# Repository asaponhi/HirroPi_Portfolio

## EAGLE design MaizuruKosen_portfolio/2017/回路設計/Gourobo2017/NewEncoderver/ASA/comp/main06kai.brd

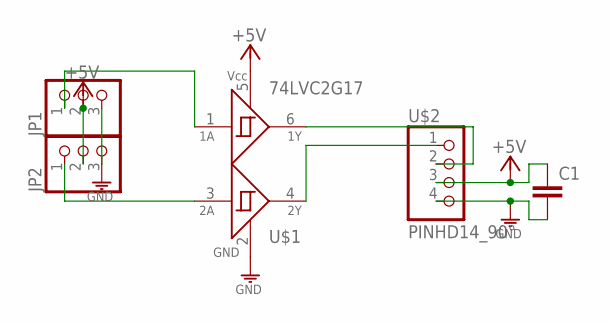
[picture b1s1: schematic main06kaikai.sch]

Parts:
C1: MLCC-2; MLCC_25
JP1, JP2: PINHD-13_90°; 1*3_90
U$1: 74LVC2G17
U$2: PINHD14_90°; 1*4_90

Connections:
+5V: C1.1, JP1.2, JP2.2, U$1.5, U$2.3
GND: C1.2, JP1.3, JP2.3, U$1.2, U$2.4
unnamed: U$1.6, U$2.2
unnamed: U$1.4, U$2.1
unnamed: JP1.1, U$1.1
unnamed: JP2.1, U$1.3

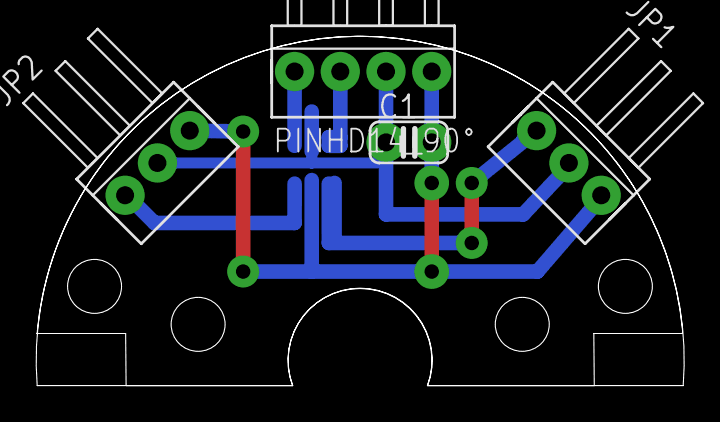
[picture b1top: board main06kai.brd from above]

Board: 2 copper layers, 36.0 x 19.4 mm, 5 parts (1 on the bottom side), 6 nets.

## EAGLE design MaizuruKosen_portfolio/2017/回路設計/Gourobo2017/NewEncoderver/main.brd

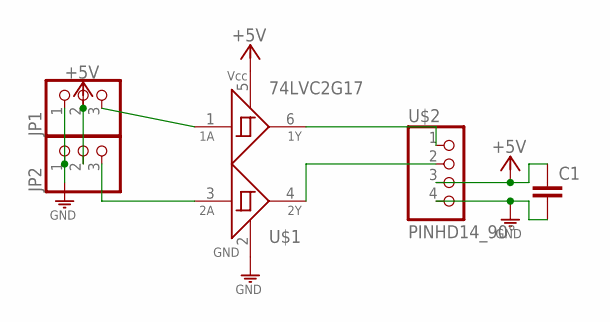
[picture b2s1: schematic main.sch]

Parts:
C1: MLCC-2; MLCC_25
JP1, JP2: PINHD-13_90°; 1*3_90
U$1: 74LVC2G17
U$2: PINHD14_90°; 1*4_90

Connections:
+5V: C1.1, JP1.2, JP2.2, U$1.5, U$2.3
GND: C1.2, JP1.1, JP2.1, U$1.2, U$2.4
unnamed: U$1.6, U$2.1
unnamed: U$1.4, U$2.2
unnamed: JP1.3, U$1.1
unnamed: JP2.3, U$1.3

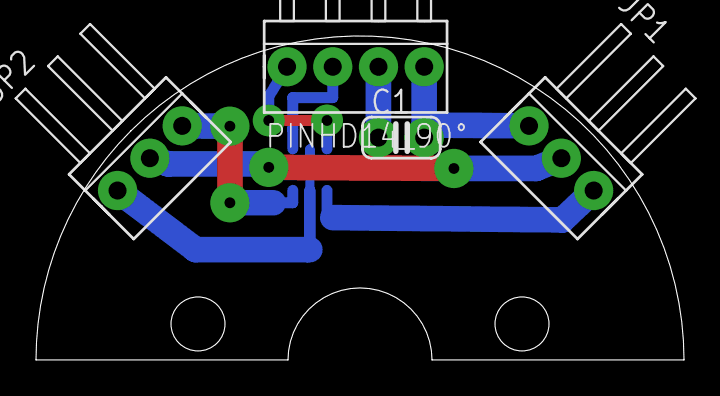
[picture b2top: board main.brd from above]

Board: 2 copper layers, 36.0 x 18.0 mm, 5 parts (1 on the bottom side), 6 nets.

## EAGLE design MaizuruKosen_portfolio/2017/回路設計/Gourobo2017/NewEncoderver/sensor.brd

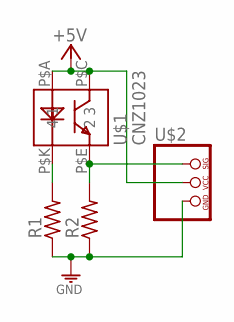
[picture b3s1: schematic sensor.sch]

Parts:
R1, R2: RESISTORS; R_3216
U$1: CNZ1023
U$2: PINHD-SENSOR; 1*03(KIKAKU)

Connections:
+5V: U$1.P$A (1), U$1.P$C (3), U$2.VCC
GND: R1.1, R2.1, U$2.GND
unnamed: R1.2, U$1.P$K (4)
unnamed: R2.2, U$1.P$E (2), U$2.SIG

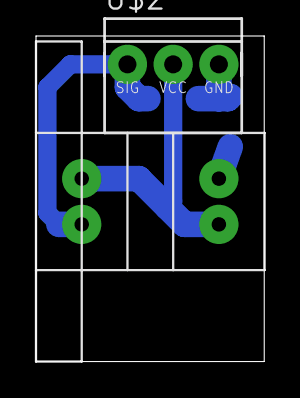
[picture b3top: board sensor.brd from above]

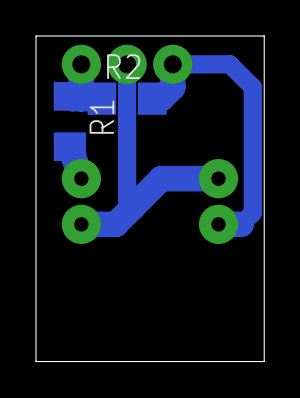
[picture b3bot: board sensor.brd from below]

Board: 2 copper layers, 12.7 x 18.1 mm, 4 parts (2 on the bottom side), 4 nets.

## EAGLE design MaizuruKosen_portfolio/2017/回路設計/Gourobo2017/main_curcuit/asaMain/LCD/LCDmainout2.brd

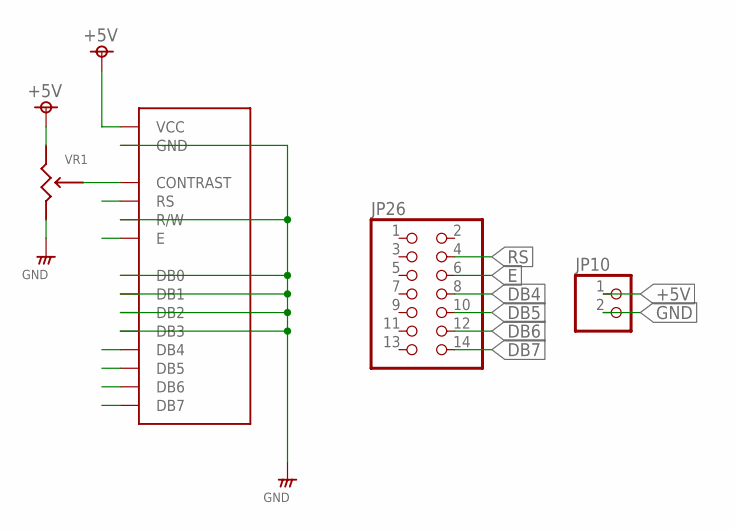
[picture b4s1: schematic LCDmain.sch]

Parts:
JP10: PINHD-1X2"; 1*02
JP26: PINHD-2X7; 2X07
U$1: LCD_16X2
VR1: R-TRIM-3-L; R_TRIM3

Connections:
+5V: JP10.1, U$1.P$1 (VCC), VR1.1
DB4: JP26.8, U$1.P$11 (DB4)
DB5: JP26.10, U$1.P$12 (DB5)
DB6: JP26.12, U$1.P$13 (DB6)
DB7: JP26.14, U$1.P$14 (DB7)
E: JP26.6, U$1.P$6 (E)
GND: JP10.2, U$1.P$2 (GND), U$1.P$5 (R/W), U$1.P$7 (DB0), U$1.P$8 (DB1), U$1.P$9 (DB2), U$1.P$10 (DB3), VR1.3
unnamed: U$1.P$3 (CONTRAST), VR1.2
RS: JP26.4, U$1.P$4 (RS)

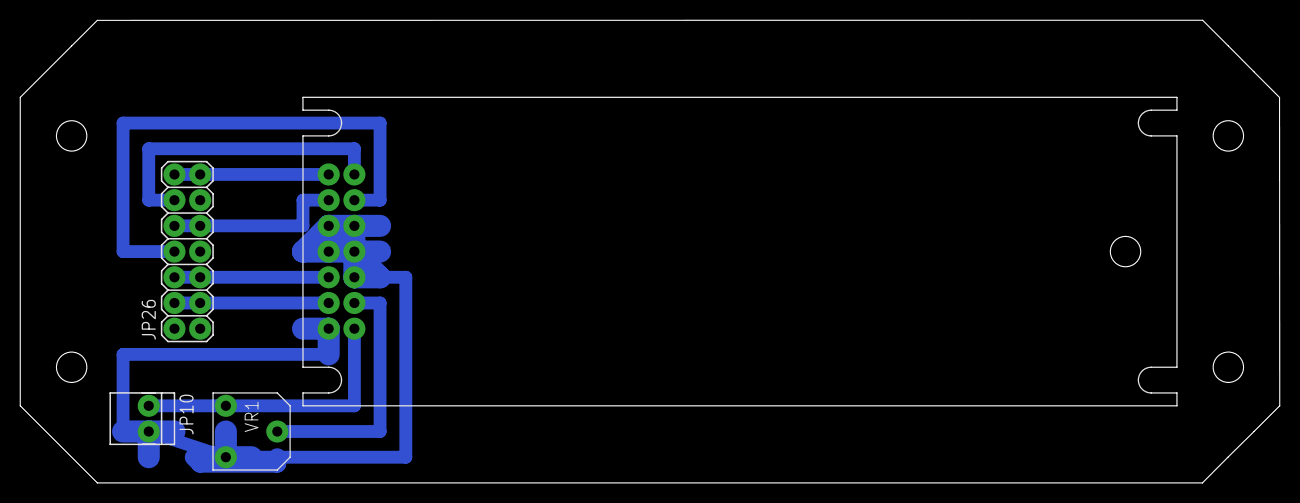
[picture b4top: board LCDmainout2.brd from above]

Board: 2 copper layers, 124.5 x 45.7 mm, 4 parts (0 on the bottom side), 9 nets.

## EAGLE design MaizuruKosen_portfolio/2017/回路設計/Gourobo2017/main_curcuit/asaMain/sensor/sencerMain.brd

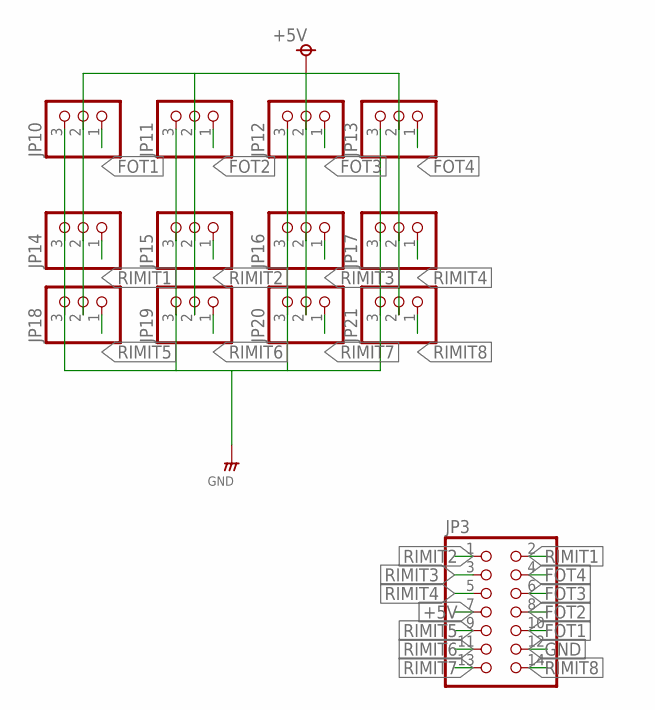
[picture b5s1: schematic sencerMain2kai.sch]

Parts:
JP3: PINHD-2X7; 2X07
JP10, JP11, JP12, JP13, JP14, JP15, JP16, JP17, JP18, JP19, JP20, JP21: PINHD-1X3-1; 1*03

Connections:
+5V: JP3.7, JP10.2, JP11.2, JP12.2, JP13.2, JP14.2, JP15.2, JP16.2, JP17.2, JP18.2, JP19.2, JP20.2, JP21.2
FOT1: JP3.10, JP10.1 (3)
FOT2: JP3.8, JP11.1 (3)
FOT3: JP3.6, JP12.1 (3)
FOT4: JP3.4, JP13.1 (3)
GND: JP3.12, JP10.3 (1), JP11.3 (1), JP13.3 (1), JP14.3 (1), JP15.3 (1), JP17.3 (1), JP18.3 (1), JP19.3 (1), JP21.3 (1)
unnamed: JP12.3 (1), JP16.3 (1), JP20.3 (1)
RIMIT1: JP3.2, JP14.1 (3)
RIMIT2: JP3.1, JP15.1 (3)
RIMIT3: JP3.3, JP16.1 (3)
RIMIT4: JP3.5, JP17.1 (3)
RIMIT5: JP3.9, JP18.1 (3)
RIMIT6: JP3.11, JP19.1 (3)
RIMIT7: JP3.13, JP20.1 (3)
RIMIT8: JP3.14, JP21.1 (3)

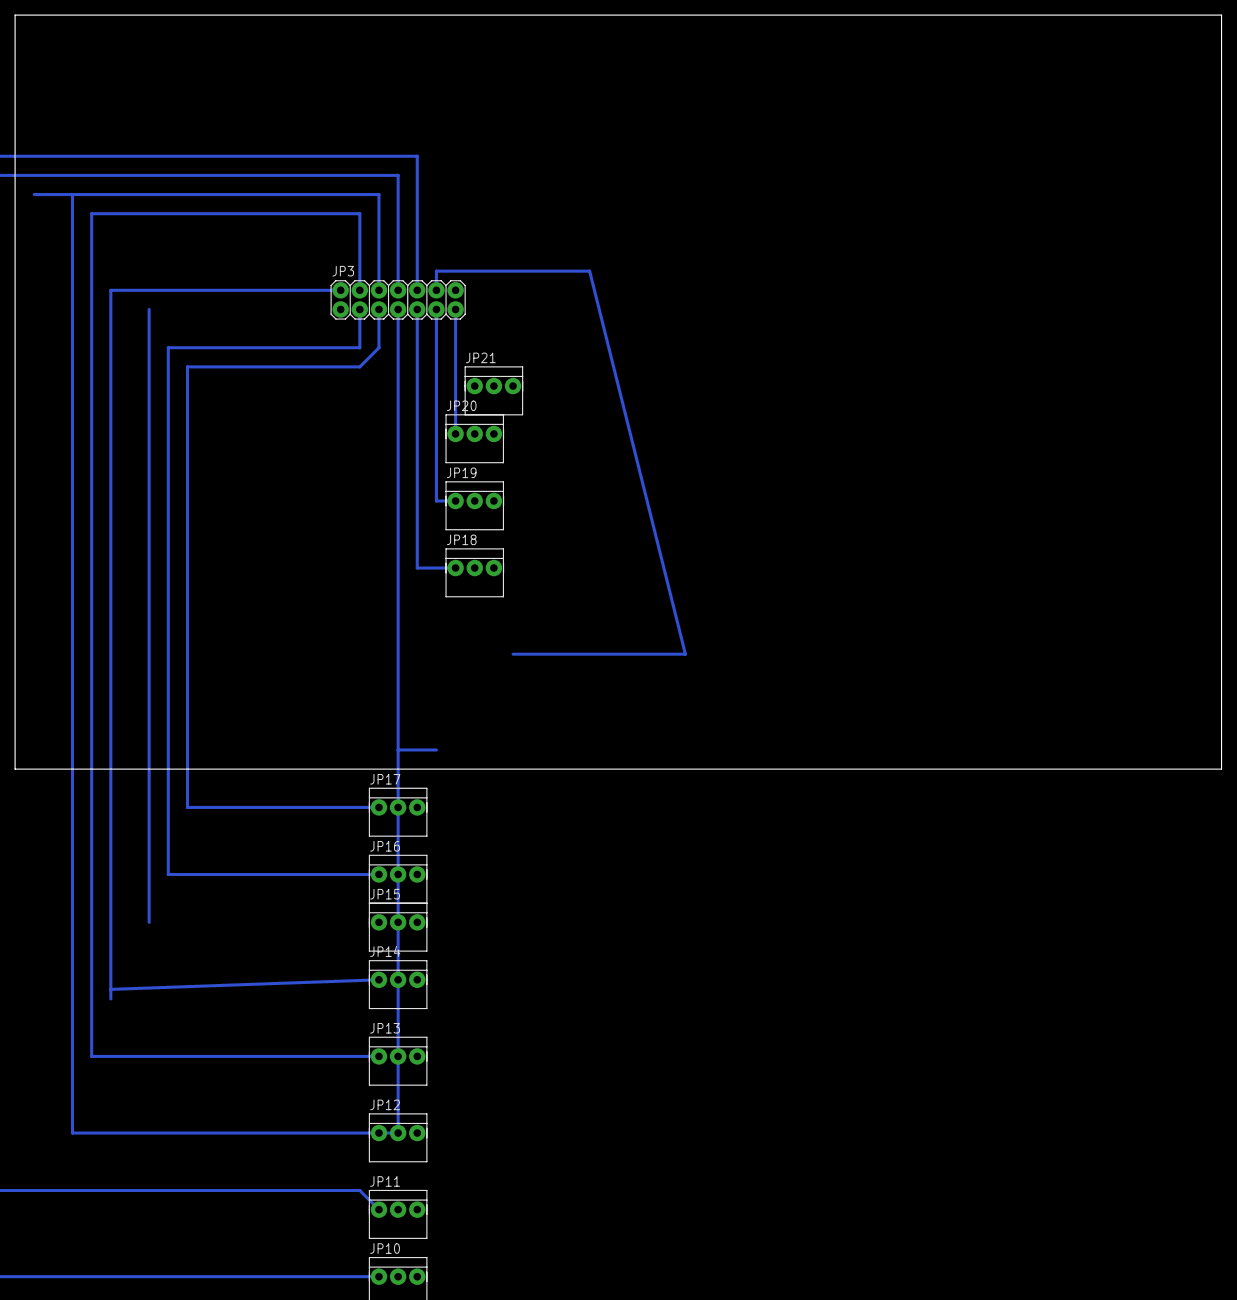
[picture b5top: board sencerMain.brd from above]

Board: 2 copper layers, 13 parts (0 on the bottom side), 15 nets.
